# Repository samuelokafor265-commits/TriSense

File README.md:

# TriSense
It's a general-purpose portable sensing node, so it fits anywhere you need to measure pressure and distance wirelessly on battery power:
Weather and environment monitoring: the pressure sensor tracks barometric changes and altitude, and the ESP32's Wi-Fi/Bluetooth sends data to a phone or cloud dashboard.
Drones and robots: altitude hold from the pressure sensor, plus obstacle avoidance or landing-height sensing from the time-of-flight sensor.
Proximity and occupancy detection: smart doors, people counting, or gesture and presence sensing.
Liquid or fill-level monitoring: the ToF sensor measures distance to the surface in tanks, bins, or water reservoirs.
Indoor navigation or floor detection: pressure changes can tell which floor of a building a device is on.
Data loggers and IoT nodes: with the LiPo and USB charging, it can run untethered in the field, which suits remote or off-grid deployments such as solar-powered stations.
Teaching and prototyping: it's a good reference board for learning I2C, level shifting, and power-path design.
The light-sensing circuit (LDR with a transistor driving an LED) could add automatic lighting or day/night detection.

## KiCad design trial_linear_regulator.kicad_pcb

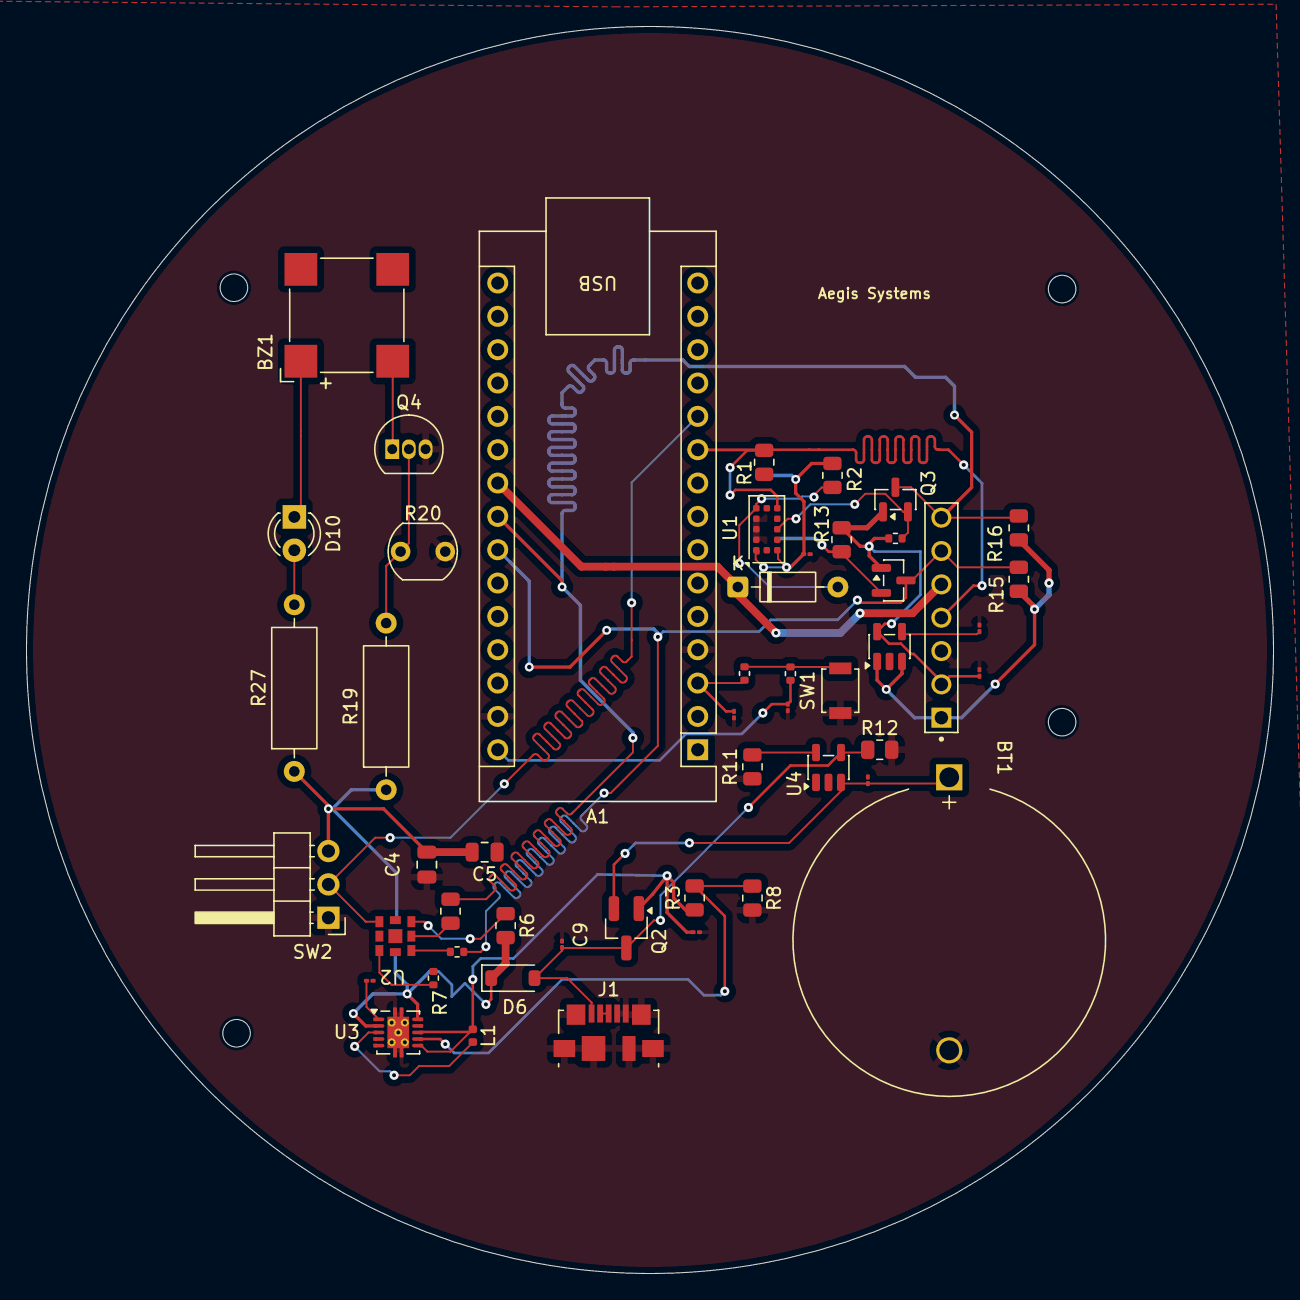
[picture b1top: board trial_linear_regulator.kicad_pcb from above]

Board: 4 copper layers, 95.0 x 95.0 mm, 54 parts (0 on the bottom side), 32 nets.

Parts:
A1: Arduino_Nano_ESP32; Arduino_Nano
BT1: Battery_Cell; BatteryHolder_MYOUNG_BS-07-A1BJ001_CR2032
BZ1: CMT-8504-100; MagneticBuzzer_CUI_CMT-8504-100-SMT
C1: 0.1uF; C_01005_0402Metric
C3: 2.2uF; C_01005_0402Metric
C4, C5: 100nF; C_0805_2012Metric
C6: 1uF; C_01005_0402Metric
C7, C9, C10: 4.7uF; C_01005_0402Metric
C8: 22uF; C_01005_0402Metric
C11: 470pF; C_01005_0402Metric
C20: 4u7; C_01005_0402Metric
D2: 1N4148; D_DO-35_SOD27_P7.62mm_Horizontal
D6: D_Schottky; D_SOD-123
D10: LED; LED_D3.0mm
H1, H2, H3, H4: MountingHole; MountingHole_2.1mm
J1: USB_B_Micro; USB_Micro-B_Molex_47346-0001
J2: SSK01-MPH-254-A7; SAMESKY_SSK01-MPH-254-A7
L1: 2.2uH; L_0402_1005Metric
Q2: Q_PMOS_DSG; SOT-23_Handsoldering
Q3, Q5: BSS138; SOT-23
Q4: BC547; TO-92_Inline
R1, R2, R11, R12, R13, R15, R16: 10k; R_0805_2012Metric
R3: 2M; R_0805_2012Metric
R5, R7: 4.7k; R_0402_1005Metric
R6, R71: 4.7k; R_0805_2012Metric
R8: 180k; R_0805_2012Metric
R9: 10K; R_0402_1005Metric
R10: 100R; R_0402_1005Metric
R14: 10k; R_0402_1005Metric
R19: 1k; R_Axial_DIN0309_L9.0mm_D3.2mm_P12.70mm_Horizontal
R20: LDR07; R_LDR_5.1x4.3mm_P3.4mm_Vertical
R27: 470; R_Axial_DIN0309_L9.0mm_D3.2mm_P12.70mm_Horizontal
SW1: SW_Push; SW_SPST_B3U-1000P
SW2: SW_SPDT; PinHeader_1x03_P2.54mm_Horizontal
U1: VL53L1CXV0FY1; ST_VL53L1x
U2: BMP585; LGA9_BMP585_BOS
U3: TPS61200DRC; Texas_S-PVSON-N10_ThermalVias
U4: MCP73831-2-OT; SOT-23-5
U5: MIC5205-2.8YM5; SOT-23-5

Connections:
+2.8V: C1.1, R1.1, R2.1, U1.1 (AVDDVCSEL), U1.11 (AVDD)
+2V8: C3.1, J2.2, Q3.1 (G), Q5.1 (G), R13.1, R14.1, U5.5 (OUT)
+5V: A1.30 (VIN), C4.1, C5.2, C8.1, D6.1 (K), R6.2, R7.1, R9.1, R19.1, R27.1, SW2.3 (C), U2.4 (VDDIO), U2.8 (VDD), U3.2 (VOUT), U3.10 (FB)
/GPIO1: A1.10 (D7), J2.4, R1.2, U1.7 (GPIO1)
/I2C_GPIO: A1.11 (D8), SW2.2 (B), U2.5 (INT)
/SCL_2.8V: Q5.2 (S), R13.2, U1.10 (SCL)
/SDA_2.8V: Q3.2 (S), R14.2, U1.9 (SDA)
/XSHUT: A1.22 (A3), D2.1 (K), J2.5
/XSHUT_2.8V: D2.2 (A), R2.2, U1.5 (XSHUT)
GND: A1.4 (GND), A1.29 (GND), BT1.2 (-), C1.2, C3.2, C4.2, C5.1, C6.2, C7.2, C8.2, C9.2, C10.2, C11.2, C20.2, J1.4 (ID), J1.5 (GND), J1.6 (Shield), J2.3, Q4.3 (E), R8.2, R11.2, R12.2, R20.2, SW1.1, SW2.1 (A), U1.2 (AVSSVCSEL), U1.3 (GND), U1.4 (GND), U1.6 (GND), U1.12 (GND), U3.4 (PGND), U3.9 (GND), U3.11 (PAD), U4.2 (V_{SS}), U5.2 (GND)
unnamed: A1.3 (~RESET), C20.1, R10.2
unnamed: BT1.1 (+), C10.1, Q2.2 (S), U4.3 (V_{BAT})
unnamed: BZ1.2 (+), Q4.1 (C)
unnamed: BZ1.1 (-), D10.1 (K)
unnamed: C9.1, D6.2 (A), J1.1 (VBUS), Q2.3 (G), R12.1, U4.4 (V_{DD})
unnamed: D10.2 (A), R27.2
unnamed: J1.2 (D-), J1.3 (D+)
unnamed: C7.1, L1.1, Q2.1 (D), R3.1, U3.5 (VIN), U3.6 (EN), U3.8 (PS)
unnamed: Q4.2 (B), R19.2, R20.1
unnamed: R9.2, R10.1, SW1.2
unnamed: R7.2, U2.7 (CSB)
unnamed: R5.1, U2.1 (SCX)
unnamed: R6.1, U2.3 (SDO)
unnamed: R71.1, U2.2 (SDX)
unnamed: L1.2, U3.3 (L)
unnamed: R3.2, R8.1, U3.7 (UVLO)
unnamed: C6.1, U3.1 (VAUX)
unnamed: R11.1, U4.5 (PROG)
unnamed: C11.1, U5.4 (BP)
SCL: A1.24 (SCL/A5), J2.6, Q5.3 (D), R5.2, R15.2
SDA: A1.23 (SDA/A4), J2.7, Q3.3 (D), R16.2, R71.2
VIN: J2.1, R15.1, R16.1, U5.1 (IN), U5.3 (EN)
